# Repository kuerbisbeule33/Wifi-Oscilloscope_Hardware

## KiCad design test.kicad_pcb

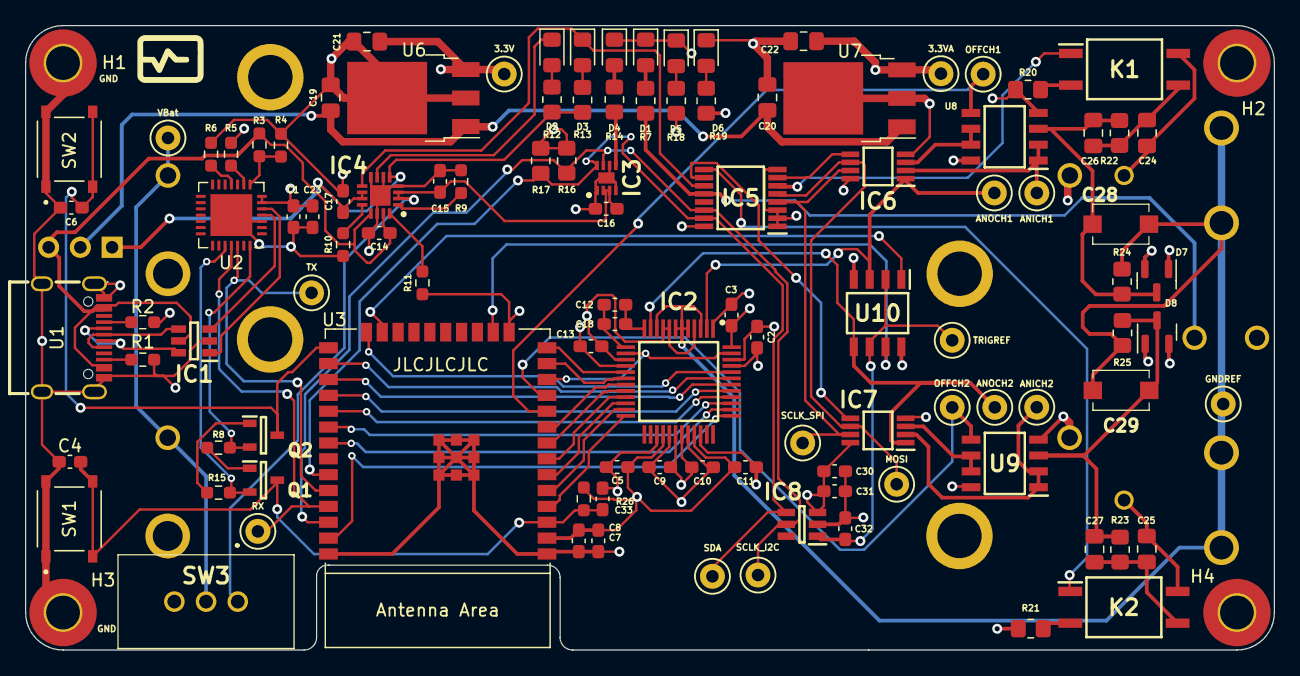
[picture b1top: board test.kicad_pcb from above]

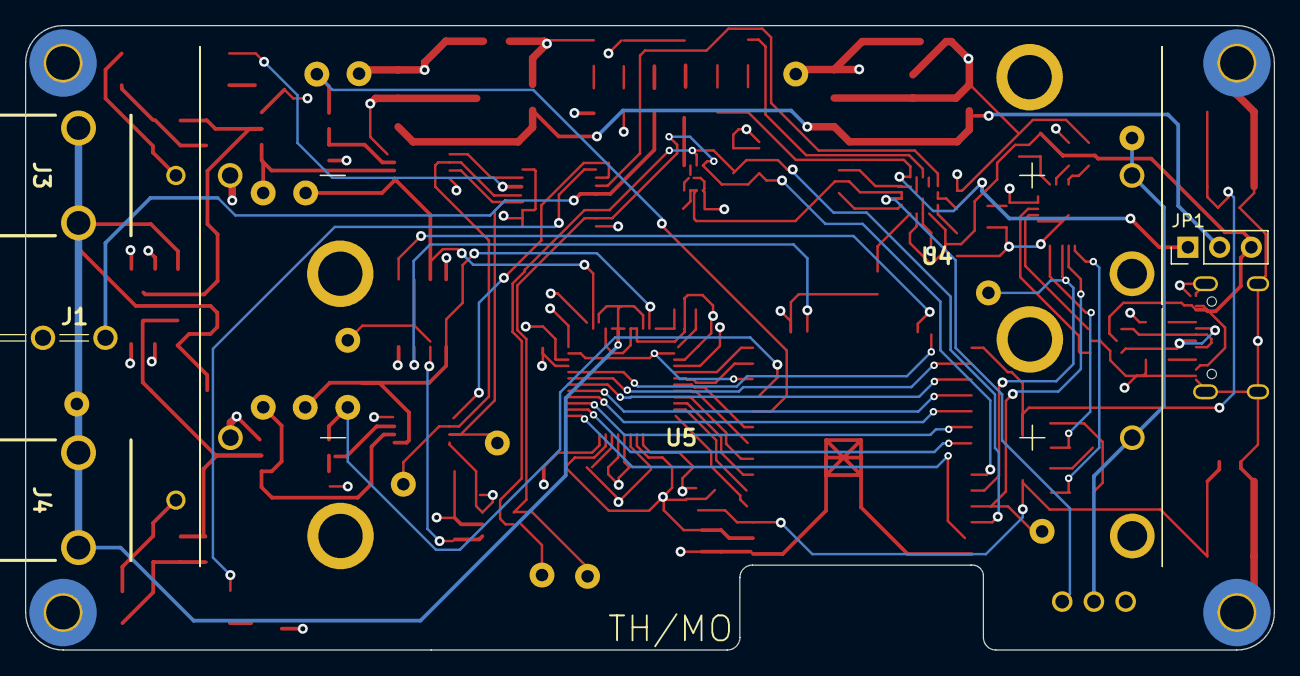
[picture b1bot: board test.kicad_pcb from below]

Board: 4 copper layers, 100.0 x 50.0 mm, 117 parts (6 on the bottom side), 85 nets.

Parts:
C1, C2, C3, C4, C5, C6, C8, C9, C10, C11, C12, C13, C16, C31, C32, C33: 0.1u; C_0603_1608Metric_Pad1.08x0.95mm_HandSolder
C7: 22u; C_0603_1608Metric_Pad1.08x0.95mm_HandSolder
C14: 1u; C_0603_1608Metric_Pad1.08x0.95mm_HandSolder
C15, C17: 4u7; C_0603_1608Metric_Pad1.08x0.95mm_HandSolder
C18, C30: 10u; C_0603_1608Metric_Pad1.08x0.95mm_HandSolder
C19, C20: 10u; C_0805_2012Metric_Pad1.18x1.45mm_HandSolder
C21, C22: 2.2u; C_0805_2012Metric_Pad1.18x1.45mm_HandSolder
C23: 4.7u; C_0603_1608Metric_Pad1.08x0.95mm_HandSolder
C24, C25: 100n; C_0805_2012Metric_Pad1.18x1.45mm_HandSolder
C26, C27: 5p; C_0805_2012Metric_Pad1.18x1.45mm_HandSolder
C28, C29: Var_25p; JZ300
D1: Status; LED_0805_2012Metric_Pad1.15x1.40mm_HandSolder
D2: LED_ValidSource; LED_0805_2012Metric_Pad1.15x1.40mm_HandSolder
D3: LED_Charging; LED_0805_2012Metric_Pad1.15x1.40mm_HandSolder
D4: LOW_BATTERY; LED_0805_2012Metric_Pad1.15x1.40mm_HandSolder
D5: 3.3V; LED_0805_2012Metric_Pad1.15x1.40mm_HandSolder
D6: 3.3VA; LED_0805_2012Metric_Pad1.15x1.40mm_HandSolder
D7, D8: BAT54S; SOT-23
H1, H3: GND; MountingHole_2.7mm_Pad_TopBottom
H2, H4: MountingHole; MountingHole_2.7mm_Pad_TopBottom
IC1: USBLC6-2SC6
IC2: AD9288BSTZ-40; QFP50P900X900X160-48N-AD9288
IC3: MAX17048G+T10
IC4: BQ24074RGTR
IC5: TCA9534APWR; SOP65P640X120-16N
IC6, IC7: MCP6S91-E_MS
IC8: MCP4726A0T-E_CH; MCP4726A1T-E_CH
J1: PWM; 725996-2
J3, J4: 73100-0105
JP1: Power_Select; PinHeader_1x03_P2.54mm_Vertical
K1, K2: AQY210EHAX
Q1, Q2: SS8050-G; SOT95P240X115-3N
R1, R2: 5k1; R_0603_1608Metric_Pad0.98x0.95mm_HandSolder
R3: 22.1k; R_0603_1608Metric_Pad0.98x0.95mm_HandSolder
R4: 47.5k; R_0603_1608Metric_Pad0.98x0.95mm_HandSolder
R5: 2k; R_0603_1608Metric_Pad0.98x0.95mm_HandSolder
R6, R8, R9, R15, R26: 10k; R_0603_1608Metric_Pad0.98x0.95mm_HandSolder
R7, R12, R13, R14, R18, R19: 1k5; R_0805_2012Metric_Pad1.20x1.40mm_HandSolder
R10: 1k; R_0603_1608Metric_Pad0.98x0.95mm_HandSolder
R11: 820; R_0603_1608Metric_Pad0.98x0.95mm_HandSolder
R16, R17: 6k8; R_0805_2012Metric_Pad1.20x1.40mm_HandSolder
R20, R21: 1k; R_0805_2012Metric_Pad1.20x1.40mm_HandSolder
R22, R23: 900k; R_0805_2012Metric_Pad1.20x1.40mm_HandSolder
R24, R25: 100k; R_0805_2012Metric_Pad1.20x1.40mm_HandSolder
SW1: Reset; SW_TS-1187A-B-A-B
SW2: Button; SW_TS-1187A-B-A-B
SW3: SW_DPDT_x2; 25136NAH6
TP1: VBat; TestPoint_Keystone_5000-5004_Miniature
TP2: 3.3V; TestPoint_Keystone_5000-5004_Miniature
TP3: 3.3VA; TestPoint_Keystone_5000-5004_Miniature
TP4: GNDREF; TestPoint_Keystone_5000-5004_Miniature
TP5: ANICH1; TestPoint_Keystone_5000-5004_Miniature
TP6: ANICH2; TestPoint_Keystone_5000-5004_Miniature
TP7: ANOCH1; TestPoint_Keystone_5000-5004_Miniature
TP8: ANOCH2; TestPoint_Keystone_5000-5004_Miniature
TP9: OFFCH1; TestPoint_Keystone_5000-5004_Miniature
TP10: OFFCH2; TestPoint_Keystone_5000-5004_Miniature
TP11: TRIGREF; TestPoint_Keystone_5000-5004_Miniature
TP12: SCLK_I2C; TestPoint_Keystone_5000-5004_Miniature
TP13: SDA; TestPoint_Keystone_5000-5004_Miniature
TP14: MOSI; TestPoint_Keystone_5000-5004_Miniature
TP15: SCLK_SPI; TestPoint_Keystone_5000-5004_Miniature
TP16: TX; TestPoint_Keystone_5000-5004_Miniature
TP17: RX; TestPoint_Keystone_5000-5004_Miniature
U1: USB-TYPE-C-018
U2: CP2102N-A02-GQFN28; QFN-28-1EP_5x5mm_P0.5mm_EP3.35x3.35mm
U3: ESP32-WROOM-E; ESP32-WROOM-32E
U4, U5: 1043
U6, U7: LD39150DT33; TO-252-3_TabPin2
U8, U9, U10: MCP6022T-I_SN

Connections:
+3.3VA: C3.1, C9.1, C10.1, C22.1, C30.1, C31.1, D7.2, D8.2, IC2.30 (VD_2), IC2.31 (VD_3), IC2.48 (VD_4), IC6.8 (VDD), IC7.8 (VDD), IC8.3 (VDD), R19.2, TP3.1, U7.3 (VO), U8.8 (V+), U9.8 (V+), U10.8 (V+)
+3V3: C1.1, C2.1, C5.1, C7.1, C8.1, C11.1, C13.1, C21.1, C23.1, IC2.4 (DFS), IC2.8 (S1), IC2.9 (S2), IC2.15 (VDD_1), IC2.28 (VDD_2), IC2.33 (VDD_3), IC2.46 (VDD_4), IC5.16 (VCC), R5.1, R16.2, R17.2, R18.2, R26.2, TP2.1, U2.6 (VDD), U2.7 (VREGIN), U3.2 (3V3), U6.3 (VO)
+5V: C14.1, IC1.5 (VBUS), IC4.13 (IN), IC4.15 (TD), JP1.3 (B), R3.1, U1.A4 (VBUS), U1.A9 (VBUS), U1.B4 (VBUS), U1.B9 (VBUS)
/CH1_D0: IC2.37 (D0A), U3.37 (GPIO23)
/CH1_D1: IC2.38 (D1A), U3.31 (GPIO19)
/CH1_D2: IC2.39 (D2A), U3.30 (GPIO18)
/CH1_D3: IC2.40 (D3A), U3.29 (GPIO5)
/CH1_D4: IC2.41 (D4A), U3.28 (GPIO17)
/CH1_D5: IC2.42 (D5A), U3.27 (GPIO16)
/CH1_D6: IC2.43 (D6A), U3.26 (ADC2_CH0/GPIO4)
/CH1_D7: IC2.44 (D7A_(MSB)), U3.24 (ADC2_CH2/GPIO2)
/CH2_D0: IC2.24 (D0B), U3.4 (SENSOR_VP/GPIO36/ADC1_CH0)
/CH2_D1: IC2.23 (D1B), U3.5 (SENSOR_VN/GPIO39/ADC1_CH3)
/CH2_D2: IC2.22 (D2B), U3.6 (GPIO34/ADC1_CH6)
/CH2_D3: IC2.21 (D3B), U3.7 (GPIO35/ADC1_CH7)
/CH2_D4: IC2.20 (D4B), U3.8 (32K_XP/GPIO32/ADC1_CH4)
/CH2_D5: IC2.19 (D5B), U3.9 (32K_XN/GPIO33/ADC1_CH5)
/CH2_D6: IC2.18 (D6B), U3.13 (MTMS/GPIO14/ADC2_CH6)
/CH2_D7: IC2.17 ((MSB)_D7B), U3.14 (MTDI/GPIO12/ADC2_CH5)
/I2S_CLK: IC2.14 (ENCB), IC2.47 (ENCA), U3.12 (ADC2_CH7/GPIO27)
/Power Supply/Alarm: IC3.5 (~ALRT), R14.2
/Power Supply/VBat+: SW3.2 (B), TP1.1, U4.1 (+), U5.1 (+)
/USB and GPIO Expander/DTR: Q2.2, R8.1, U2.28 (~DTR)
/USB and GPIO Expander/RTS: Q1.2, R15.1, U2.24 (~RTS)
/USB and GPIO Expander/Status_PWM: IC5.12 (P7), J1.1, R7.2
Analog_Out_CH1: IC2.2 (AINA), IC6.1 (VOUT), TP7.1, U10.3 (+)
Analog_Out_CH2: IC2.11 (AINB), IC7.1 (VOUT), TP8.1, U10.5 (+)
CH1_AC_Sel: IC5.6 (P2), K1.1 (Anode)
CH2_AC_Sel: IC5.9 (P4), K2.1 (Anode)
CS_Gain_CH1: IC5.7 (P3), IC6.5 (~CS)
CS_Gain_CH2: IC5.10 (P5), IC7.5 (~CS)
Charging: D3.1 (K), IC4.9 (~CHG), IC5.11 (P6)
ENABLE: C4.1, C33.1, Q1.3, R26.1, SW1.C, SW1.D, U3.3 (EN/CHIP_PU)
GND: C1.2, C2.2, C3.2, C4.2, C5.2, C6.2, C7.2, C8.2, C9.2, C10.2, C11.2, C13.2, C14.2, C15.2, C16.2, C17.2, C19.2, C20.2, C21.2, C22.2, C23.2, C30.2, C31.2, C32.2, C33.2, D1.1 (K), D4.1 (K), D5.1 (K), D6.1 (K), D7.1, D8.1, H1.1, H3.1, IC1.2 (GND), IC2.1 (GND_1), IC2.16 (GND_3), IC2.27 (GND_4), IC2.29 (GND_5), IC2.32 (GND_6), IC2.34 (GND_7), IC2.45 (GND_8), IC3.1 (CTG), IC3.4 (GND), IC3.6 (QSTRT), IC3.9 (EP_(GND)), IC4.4 (~CE), IC4.6 (EN1), IC4.8 (VSS), IC4.14 (TMR), IC4.17 (GND), IC5.1 (A0), IC5.2 (A1), IC5.3 (A2), IC5.8 (GND), IC6.4 (VSS), IC7.4 (VSS), IC8.2 (VSS), R1.2, R2.2, R4.1, R6.2, R9.1, R10.2, R11.2, R20.1, R21.1, SW1.A, SW1.B, SW2.A, SW2.B, U1.0 (SHIELD), U1.1 (SHIELD), U1.2 (SHIELD), U1.3 (SHIELD), U1.A1 (GND), U1.A12 (GND), U1.B1 (GND), U1.B12 (GND), U2.3 (GND), U2.29 (GND), U3.1 (GND), U3.15 (GND), U3.38 (GND), U3.39 (GND_THERMAL), U4.2 (-), U5.2 (-), U6.2 (GND), U7.2 (GND), U8.4 (V-), U9.4 (V-), U10.4 (V-)
GNDREF: C28.2, C29.2, IC2.3 (~AINA), IC2.5 (REFINA), IC2.6 (REFOUT), IC2.7 (REFINB), IC2.10 (~AINB), J3.1, J3.2, J4.1, J4.2, R24.2, R25.2, TP4.1
IO0: C6.1, Q2.3, SW2.C, SW2.D, U3.25 (GPIO0/BOOT/ADC2_CH1)
MOSI: IC5.5 (P1), IC6.6 (SI), IC7.6 (SI), TP14.1
unnamed: C12.1, C18.1, IC2.12 (GND_2)
unnamed: C12.2, C18.2, IC2.13 (VD_1)
unnamed: C15.1, C16.1, IC3.2 (CELL), IC3.3 (VDD), IC4.2 (BAT_1), IC4.3 (BAT_2), SW3.1 (A)
unnamed: C17.1, IC4.5 (EN2), IC4.10 (OUT_1), IC4.11 (OUT_2), JP1.1 (A), R12.2, R13.2
unnamed: C19.1, C20.1, JP1.2 (C), U6.1 (VI), U7.1 (VI)
unnamed: C24.1, C26.2, K1.3 (SW), R22.2
unnamed: C24.2, J3.3, K1.4 (SW)
unnamed: C25.1, C27.2, K2.3 (SW), R23.2
unnamed: C25.2, J4.3, K2.4 (SW)
unnamed: C26.1, C28.1, D7.3, R22.1, R24.1, U8.3 (+)
unnamed: C27.1, C29.1, D8.3, R23.1, R25.1, U9.3 (+)
unnamed: C32.1, IC8.1 (VOUT), TP11.1, U10.2 (-), U10.6 (-)
unnamed: D1.2 (A), R7.1
unnamed: D2.1 (K), IC4.7 (~PGOOD)
unnamed: D2.2 (A), R12.1
unnamed: D3.2 (A), R13.1
unnamed: D4.2 (A), R14.1
unnamed: D5.2 (A), R18.1
unnamed: D6.2 (A), R19.1
unnamed: IC1.1 (IO1_1), U2.5 (D-)
unnamed: IC1.3 (IO2_1), U2.4 (D+)
unnamed: IC1.4 (IO2_2), U1.A6 (D+), U1.B6 (D+)
unnamed: IC1.6 (IO1_2), U1.A7 (D-), U1.B7 (D-)
unnamed: IC4.1 (TS), R9.2
unnamed: IC4.12 (ILIM), R10.1
unnamed: IC4.16 (ISET), R11.1
unnamed: IC6.2 (CH0), TP5.1, U8.1, U8.2 (-)
unnamed: IC6.3 (VREF), U8.6 (-), U8.7
unnamed: IC7.2 (CH0), TP6.1, U9.1, U9.2 (-)
unnamed: IC7.3 (VREF), U9.6 (-), U9.7
unnamed: K1.2 (Kathode), R20.2
unnamed: K2.2 (Kathode), R21.2
unnamed: Q1.1, R8.2
unnamed: Q2.1, R15.2
unnamed: R1.1, U1.B5 (CC2)
unnamed: R2.1, U1.A5 (CC1)
unnamed: R3.2, R4.2, U2.8 (VBUS)
unnamed: R5.2, U2.9 (~RST)
unnamed: R6.1, U2.11 (~SUSPEND)
Offset_CH1: TP9.1, U3.10 (DAC_1/ADC2_CH8/GPIO25), U8.5 (+)
Offset_CH2: TP10.1, U3.11 (DAC_2/ADC2_CH9/GPIO26), U9.5 (+)
RX: TP17.1, U2.25 (RXD), U3.35 (U0TXD/GPIO1)
SCLK_SPI: IC5.4 (P0), IC6.7 (SCK), IC7.7 (SCK), TP15.1
SCL_I2C: IC3.7 (SCL), IC5.14 (SCL), IC8.5 (SCL), R16.1, TP12.1, U3.36 (GPIO22)
SDA: IC3.8 (SDA), IC5.15 (SDA), IC8.4 (SDA), R17.1, TP13.1, U3.33 (GPIO21)
TX: TP16.1, U2.26 (TXD), U3.34 (U0RXD/GPIO3)
Trigger_CH1: U3.23 (MTDO/GPIO15/ADC2_CH3), U10.1
Trigger_CH2: U3.16 (MTCK/GPIO13/ADC2_CH4), U10.7

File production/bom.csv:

Designator,Footprint,Quantity,Value,LCSC Part #
"C1, C10, C11, C12, C13, C16, C2, C3, C31, C32, C4, C5, C6, C8, C9",0603,15,0.1u,
C14,0603,1,1u,
"C15, C17",0603,2,4u7,
"C18, C30",0603,2,10u,
"C19, C20, C21, C22",0805,4,10u,
C23,0603,1,4.7u,
"C24, C25",0805,2,100n,
"C26, C27",0805,2,5p,
"C28, C29",JZ300,2,Var_25p,
C7,0603,1,22u,
D1,0805,1,Status,
"D10, D7, D8, D9",0805,4,D_Schottky,
D2,0805,1,LED_ValidSource,
D3,0805,1,LED_Charging,
D4,0805,1,LOW_BATTERY,
D5,0805,1,3.3V,
D6,0805,1,3.3VA,
"H1, H2, H3, H4",MountingHole_2.7mm_Pad_TopBottom,4,MountingHole,
IC1,USBLC6-2SC6,1,USBLC6-2SC6,
IC2,QFP50P900X900X160-48N-AD9288,1,AD9288BSTZ-40,
IC3,MAX17048G+T10,1,MAX17048G+T10,
IC4,BQ24074RGTR,1,BQ24074RGTR,
IC5,SOP65P640X120-16N,1,TCA9534APWR,
"IC6, IC7",MCP6S91-E_MS,2,MCP6S91-E_MS,
IC8,MCP4726A1T-E_CH,1,MCP4726A0T-E_CH,
J1,725996-2,1,PWM,
"J3, J4",73100-0105,2,~,
JP1,PinHeader_1x03_P2.54mm_Vertical,1,Power_Select,
"K1, K2",AQY210EHAX,2,AQY210EHAX,
"Q1, Q2",SOT95P240X115-3N,2,SS8050-G,
"R1, R2",0603,2,5k1,
R10,0603,1,1k,
R11,0603,1,820,
"R12, R13, R14, R18, R19, R7",0805,6,1k5,
"R15, R6, R8, R9",0603,4,10k,
"R16, R17",0805,2,6k8,
"R20, R21",0805,2,1k,
"R22, R23",0805,2,900k,
"R24, R25",0805,2,100k,
R3,0603,1,22.1k,
R4,0603,1,47.5k,
R5,0603,1,2k,
SW1,SW_TS-1187A-B-A-B,1,Reset,
SW2,SW_TS-1187A-B-A-B,1,Button,
SW3,25136NAH6,1,SW_DPDT_x2,
TP1,TestPoint_Keystone_5000-5004_Miniature,1,VBat,
TP10,TestPoint_Keystone_5000-5004_Miniature,1,OFFCH2,
TP11,TestPoint_Keystone_5000-5004_Miniature,1,TRIGREF,
TP12,TestPoint_Keystone_5000-5004_Miniature,1,SCLK_I2C,
TP13,TestPoint_Keystone_5000-5004_Miniature,1,SDA,
TP14,TestPoint_Keystone_5000-5004_Miniature,1,MOSI,
TP15,TestPoint_Keystone_5000-5004_Miniature,1,SCLK_SPI,
TP16,TestPoint_Keystone_5000-5004_Miniature,1,TX,
TP17,TestPoint_Keystone_5000-5004_Miniature,1,RX,
TP2,TestPoint_Keystone_5000-5004_Miniature,1,3.3V,
TP3,TestPoint_Keystone_5000-5004_Miniature,1,3.3VA,
TP4,TestPoint_Keystone_5000-5004_Miniature,1,GNDREF,
TP5,TestPoint_Keystone_5000-5004_Miniature,1,ANICH1,
TP6,TestPoint_Keystone_5000-5004_Miniature,1,ANICH2,
TP7,TestPoint_Keystone_5000-5004_Miniature,1,ANOCH1,
TP8,TestPoint_Keystone_5000-5004_Miniature,1,ANOCH2,
TP9,TestPoint_Keystone_5000-5004_Miniature,1,OFFCH1,
U1,USB-TYPE-C-018,1,USB-TYPE-C-018,C2927038
"U10, U8, U9",MCP6022T-I_SN,3,MCP6022T-I_SN,
U2,QFN-28-1EP_5x5mm_P0.5mm_EP3.35x3.35mm,1,CP2102N-A02-GQFN28,
U3,ESP32-WROOM-32E,1,ESP32-WROOM-E,
"U4, U5",1043,2,1043,
"U6, U7",TO-252-2,2,LD1086DT33TR,

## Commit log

2023-01-23 esp32 and power
    added first try of battery, connecotrs and esp32.
2023-01-23 first try of front end
2023-01-26 test changes
2023-02-02 added battery monitoring
2023-02-07 change esp-pins for parallel adc input and correct bootstrap pins
2023-02-07 added simpler 40Msps adc
2023-02-07 added dac and changed switch, gain
2023-02-08 grouped footprints
2023-02-08 groups new aranged
2023-02-08 added symmetric voltage and input stage
2023-02-16 changed analog
2023-02-16 Changed Power Suply to seperate sheet and added changed parts
2023-02-16 added connector part
2023-02-16 added Bus for esp and adc
2023-02-16 analog
2023-02-16 changed global labels, and delete analog file to solve merge
2023-02-16 resolve DRC on schematic
2023-02-17 layout for changed chematic
2023-02-20 small fix for jlcpcb parts detection
2023-02-22 Added ADC vor Trigger and changed Layout
    Some Traces cant be good routed
2023-02-22 new idear to arange gnd ref in layout
2023-02-22 routes
2023-02-23 Revert "routes"
    This reverts commit 9885d0ddc0879b66fa09137adfbba2dd9588932c.
2023-02-23 added values for analog front end
2023-03-01 new adc
2023-03-02 changed adc and esp chip
2023-03-08 updated circuit
2023-03-09 routing
2023-03-24 last changes
2023-04-08 fixed uart connection
2023-04-13 changed linear regulators
